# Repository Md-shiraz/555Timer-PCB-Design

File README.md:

# 555 Timer DC Motor Controller

A KiCad hardware project for an adjustable 555-timer-driven DC motor switch. An LM555 generates a control signal, and an N-channel MOSFET switches the motor on the low side. A potentiometer and diode/resistor network set the timing behavior. The design is intended for learning and prototyping; it is not a production-ready motor driver.

## Project contents

| File | Description |
| --- | --- |
| `555Timer.kicad_pro` | KiCad project settings |
| `555Timer.kicad_sch` | Circuit schematic |
| `555Timer.kicad_pcb` | PCB layout |
| `docs/control-circuit.png` | Schematic overview |
| `docs/pcb-top-view.png` | 3D view of the PCB |

Open `555Timer.kicad_pro` in KiCad to access the schematic and board together.

## How the circuit works

The LM555 (`U2`) is connected as an oscillator: its trigger and threshold inputs share the timing node, with a 100 kΩ potentiometer (`RV1`), two 1N4007 diodes, and resistors forming the timing network. The diodes provide separate paths for timing-capacitor charge and discharge. Adjusting the potentiometer changes the generated signal's timing and duty cycle.

The timer output drives the gate of `Q1`, an N-channel MOSFET. The MOSFET switches the motor (`M1`) between the positive supply and ground, so the 555 controls the motor without carrying its load current. `R3` is connected as a gate pull-down. `C1` and `C2` are 0.1 µF capacitors in the timer circuit.

This is an open-loop controller: it does not measure motor speed or regulate it against load changes. The resulting motor behavior depends on the supply, motor, potentiometer setting, and load.

## Schematic

## PCB

The board layout includes the timer and timing components, a potentiometer footprint, a MOSFET footprint, and a two-position screw terminal for the motor connection. Confirm the board's connector assignments and polarity against the schematic and PCB before wiring.

## Main components

| Reference | Part/value | Role |
| --- | --- | --- |
| `U2` | LM555xM | Timer/oscillator |
| `Q1` | N-channel MOSFET (`Q_NMOS_GDS` symbol) | Low-side motor switch |
| `M1` | DC motor (`Motor_DC` schematic symbol) | Switched load |
| `RV1` | 100 kΩ potentiometer | Timing adjustment |
| `R1`, `R2`, `R3` | 10 kΩ each | Timing and gate-bias network |
| `D1`, `D2` | 1N4007 | Timing-network steering diodes |
| `C1`, `C2` | 0.1 µF each | Timer capacitors |

The MOSFET symbol is generic; select a specific part only after checking its pinout, gate-drive requirements, voltage rating, current rating, and thermal limits for the intended motor and supply.

## Getting started

1. Install KiCad 8 or newer.
2. Open `555Timer.kicad_pro`.
3. Review the schematic and PCB together. Check the MOSFET pin mapping, motor-terminal polarity, component values, and footprints against the parts you intend to use.
4. Run the Electrical Rules Checker (ERC) on the schematic and the Design Rules Checker (DRC) on the PCB. Resolve errors and review warnings; do not assume a passing check establishes that the design is electrically or thermally suitable.
5. For fabrication, plot the required Gerber copper, solder-mask, silkscreen, and board-outline layers, and generate drill files. Inspect the generated files and confirm the manufacturer's capabilities before ordering.

## Before powering or manufacturing

- The project does not specify a validated operating-voltage or motor-current range. Establish these limits from the selected components and board layout before use.
- Verify that the MOSFET is suitable for the timer's gate voltage and the motor's startup/stall current; check dissipation and heatsinking as applicable.
- Check whether the motor needs additional transient suppression. The timing diodes are not a substitute for a flyback clamp across an inductive load.
- Check copper widths, connector ratings, clearances, soldering, and mechanical fit for the actual application.
- Start testing with a current-limited supply and an appropriate low-risk load, and monitor the MOSFET and motor for excessive heating.

This is a prototype design and should be reviewed and bench-tested before use. The included images are visual references; the KiCad schematic and PCB files are the editable design sources.

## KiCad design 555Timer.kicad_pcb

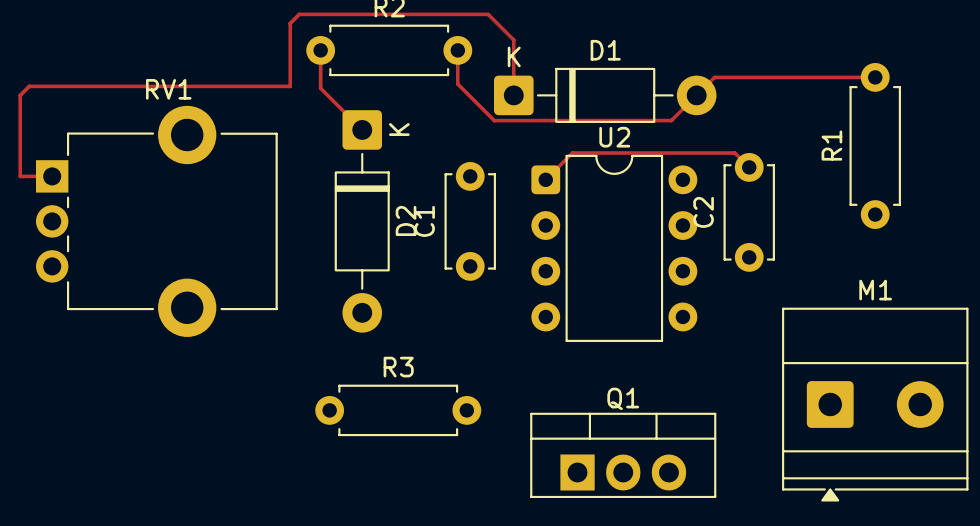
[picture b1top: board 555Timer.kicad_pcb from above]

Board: 2 copper layers, 11 parts (0 on the bottom side), 10 nets.

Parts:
C1, C2: 0.1uF; C_Disc_D5.0mm_W2.5mm_P5.00mm
D1, D2: 1N4007; D_DO-41_SOD81_P10.16mm_Horizontal
M1: Motor_DC; TerminalBlock_Phoenix_MKDS-1,5-2_1x02_P5.00mm_Horizontal
Q1: Q_NMOS_GDS; TO-220-3_Vertical
R1, R2, R3: 10k; R_Axial_DIN0207_L6.3mm_D2.5mm_P7.62mm_Horizontal
RV1: 100k; Potentiometer_Alpha_RD901F-40-00D_Single_Vertical_CircularH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
U2: LM555xM; DIP-8_W7.62mm

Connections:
Earth: C1.2, C2.2, Q1.3 (S), R3.2, U2.1 (GND)
unnamed: D1.2 (A), R1.2, R2.2, U2.7 (DISCH)
unnamed: D1.1 (K), RV1.1
unnamed: D2.2 (A), RV1.3
unnamed: D2.1 (K), R2.1
unnamed: M1.2 (-), Q1.2 (D)
unnamed: Q1.1 (G), R3.1, U2.3 (OUT)
unnamed: C2.1, U2.5 (CONT)
unnamed: C1.1, RV1.2, U2.2 (TRIG), U2.6 (THRES)
VCC: M1.1 (+), R1.1, U2.4 (~RST), U2.8 (VCC)
